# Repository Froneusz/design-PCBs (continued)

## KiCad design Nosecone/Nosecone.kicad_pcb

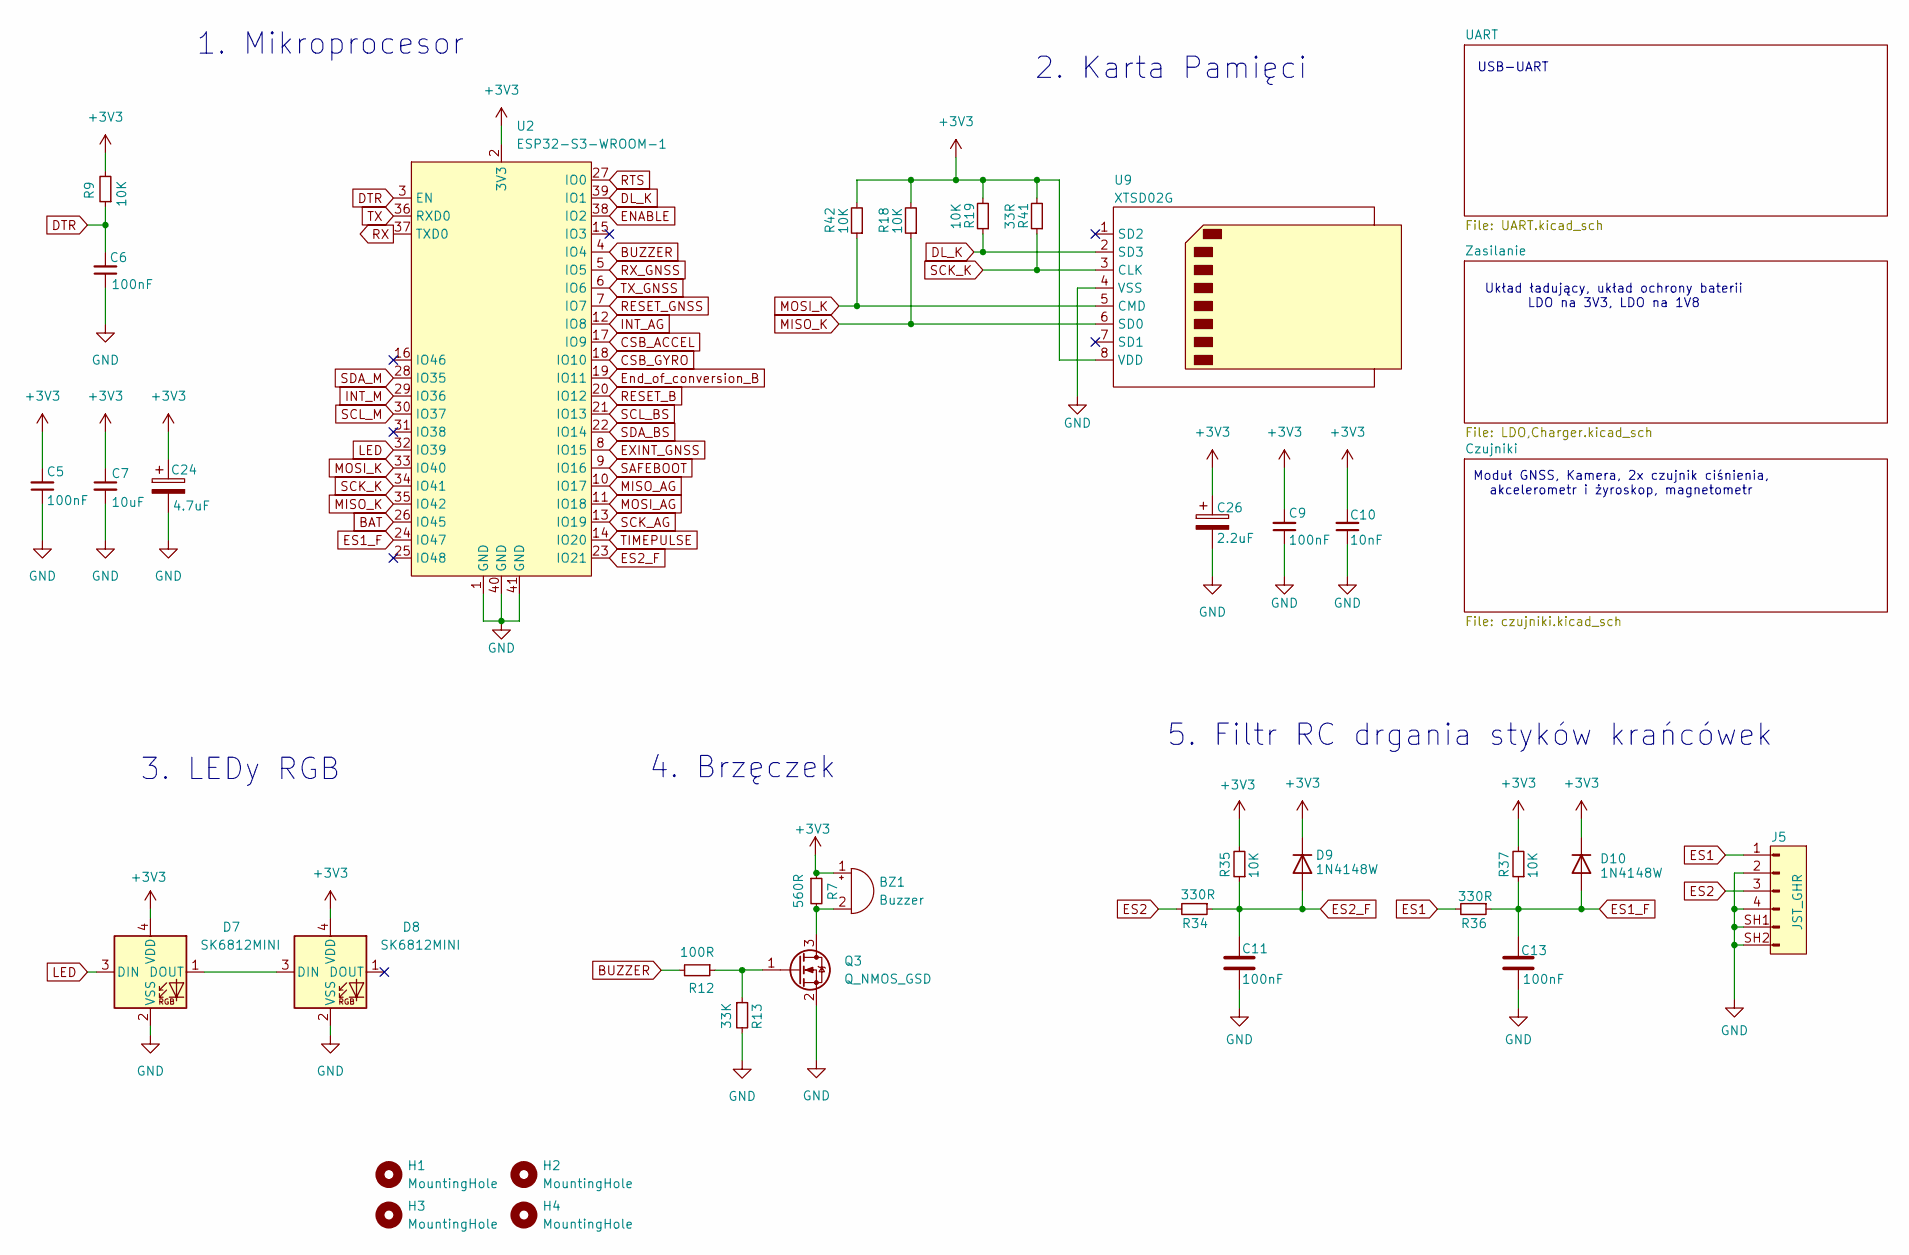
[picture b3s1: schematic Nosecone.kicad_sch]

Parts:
BZ1: Buzzer; CMT32265SMTTR
C5, C6, C9, C11, C13: 100nF; C_0402_1005Metric_Pad0.74x0.62mm_HandSolder
C7: 10uF; C_0402_1005Metric_Pad0.74x0.62mm_HandSolder
C10: 10nF; C_0402_1005Metric_Pad0.74x0.62mm_HandSolder
C24: 4.7uF; C_0402_1005Metric_Pad0.74x0.62mm_HandSolder
C26: 2.2uF; C_0402_1005Metric_Pad0.74x0.62mm_HandSolder
D7, D8: SK6812MINI; LED_SK6812MINI_PLCC4_3.5x3.5mm_P1.75mm
D9, D10: 1N4148W; D_SOD-123
H1, H2, H3, H4: MountingHole; MountingHole_3.2mm_M3_DIN965
J5: JST_GHR; JST_SM04B-GHS-TB(LF)(SN)-
Q3: Q_NMOS_GSD; SOT-23_Handsoldering
R7: 560R; R_0402_1005Metric_Pad0.72x0.64mm_HandSolder
R9, R18, R19, R35, R37, R42: 10K; R_0402_1005Metric_Pad0.72x0.64mm_HandSolder
R12: 100R; R_0402_1005Metric_Pad0.72x0.64mm_HandSolder
R13: 33K; R_0402_1005Metric_Pad0.72x0.64mm_HandSolder
R34, R36: 330R; R_0402_1005Metric_Pad0.72x0.64mm_HandSolder
R41: 33R; R_0402_1005Metric_Pad0.72x0.64mm_HandSolder
U2: ESP32-S3-WROOM-1
U9: XTSD02G; Bosch_LGA-8_2.5x2.5mm_P0.65mm_ClockwisePinNumbering

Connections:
+3V3: BZ1.1 (-), C5.2, C7.1, C9.2, C10.2, C24.1, C26.1, D7.4 (VDD), D8.4 (VDD), D9.1 (K), D10.1 (K), R7.1, R9.2, R18.2, R19.2, R35.2, R37.2, R41.2, R42.2, U2.2 (3V3), U9.8 (VDD); also elsewhere on the board
BAT: U2.26 (IO45); also elsewhere on the board
BUZZER: R12.2, U2.4 (IO4)
CSB_ACCEL: U2.17 (IO9); also elsewhere on the board
CSB_GYRO: U2.18 (IO10); also elsewhere on the board
DL_K: R19.1, U2.39 (IO1), U9.2 (SD3)
DTR: C6.2, R9.1, U2.3 (EN); also elsewhere on the board
ENABLE: U2.38 (IO2); also elsewhere on the board
ES1: J5.1, R36.2
ES1_F: C13.2, D10.2 (A), R36.1, R37.1, U2.24 (IO47)
ES2: J5.3, R34.2
ES2_F: C11.2, D9.2 (A), R34.1, R35.1, U2.23 (IO21)
EXINT_GNSS: U2.8 (IO15); also elsewhere on the board
End_of_conversion_B: U2.19 (IO11); also elsewhere on the board
GND: C5.1, C6.1, C7.2, C9.1, C10.1, C11.1, C13.1, C24.2, C26.2, D7.2 (VSS), D8.2 (VSS), J5.2, J5.4, J5.SH1 (Pin_5), J5.SH2 (Pin_6), Q3.2 (S), R13.2, U2.1 (GND), U2.40 (GND), U2.41 (GND), U9.4 (VSS); also elsewhere on the board
INT_AG: U2.12 (IO8); also elsewhere on the board
INT_M: U2.29 (IO36); also elsewhere on the board
LED: D7.3 (DIN), U2.32 (IO39)
MISO_AG: U2.10 (IO17); also elsewhere on the board
MISO_K: R18.1, U2.35 (IO42), U9.6 (SD0)
MOSI_AG: U2.11 (IO18); also elsewhere on the board
MOSI_K: R42.1, U2.33 (IO40), U9.5 (CMD)
unnamed: BZ1.2 (+), Q3.3 (D), R7.2
unnamed: D7.1 (DOUT), D8.3 (DIN)
unnamed: Q3.1 (G), R12.1, R13.1
RESET_B: U2.20 (IO12); also elsewhere on the board
RESET_GNSS: U2.7 (IO7); also elsewhere on the board
RTS: U2.27 (IO0); also elsewhere on the board
RX: U2.37 (TXD0); also elsewhere on the board
RX_GNSS: U2.5 (IO5); also elsewhere on the board
SAFEBOOT: U2.9 (IO16); also elsewhere on the board
SCK_AG: U2.13 (IO19); also elsewhere on the board
SCK_K: R41.1, U2.34 (IO41), U9.3 (CLK)
SCL_BS: U2.21 (IO13); also elsewhere on the board
SCL_M: U2.30 (IO37); also elsewhere on the board
SDA_BS: U2.22 (IO14); also elsewhere on the board
SDA_M: U2.28 (IO35); also elsewhere on the board
TIMEPULSE: U2.14 (IO20); also elsewhere on the board
TX: U2.36 (RXD0); also elsewhere on the board
TX_GNSS: U2.6 (IO6); also elsewhere on the board

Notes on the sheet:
1. Mikroprocesor
Moduł GNSS, Kamera, 2x czujnik ciśnienia, akcelerometr i żyroskop, magnetometr
Układ ładujący, układ ochrony baterii LDO na 3V3, LDO na 1V8
2. Karta Pamięci
USB-UART
3. LEDy RGB
4. Brzęczek
5. Filtr RC drgania styków krańcówek

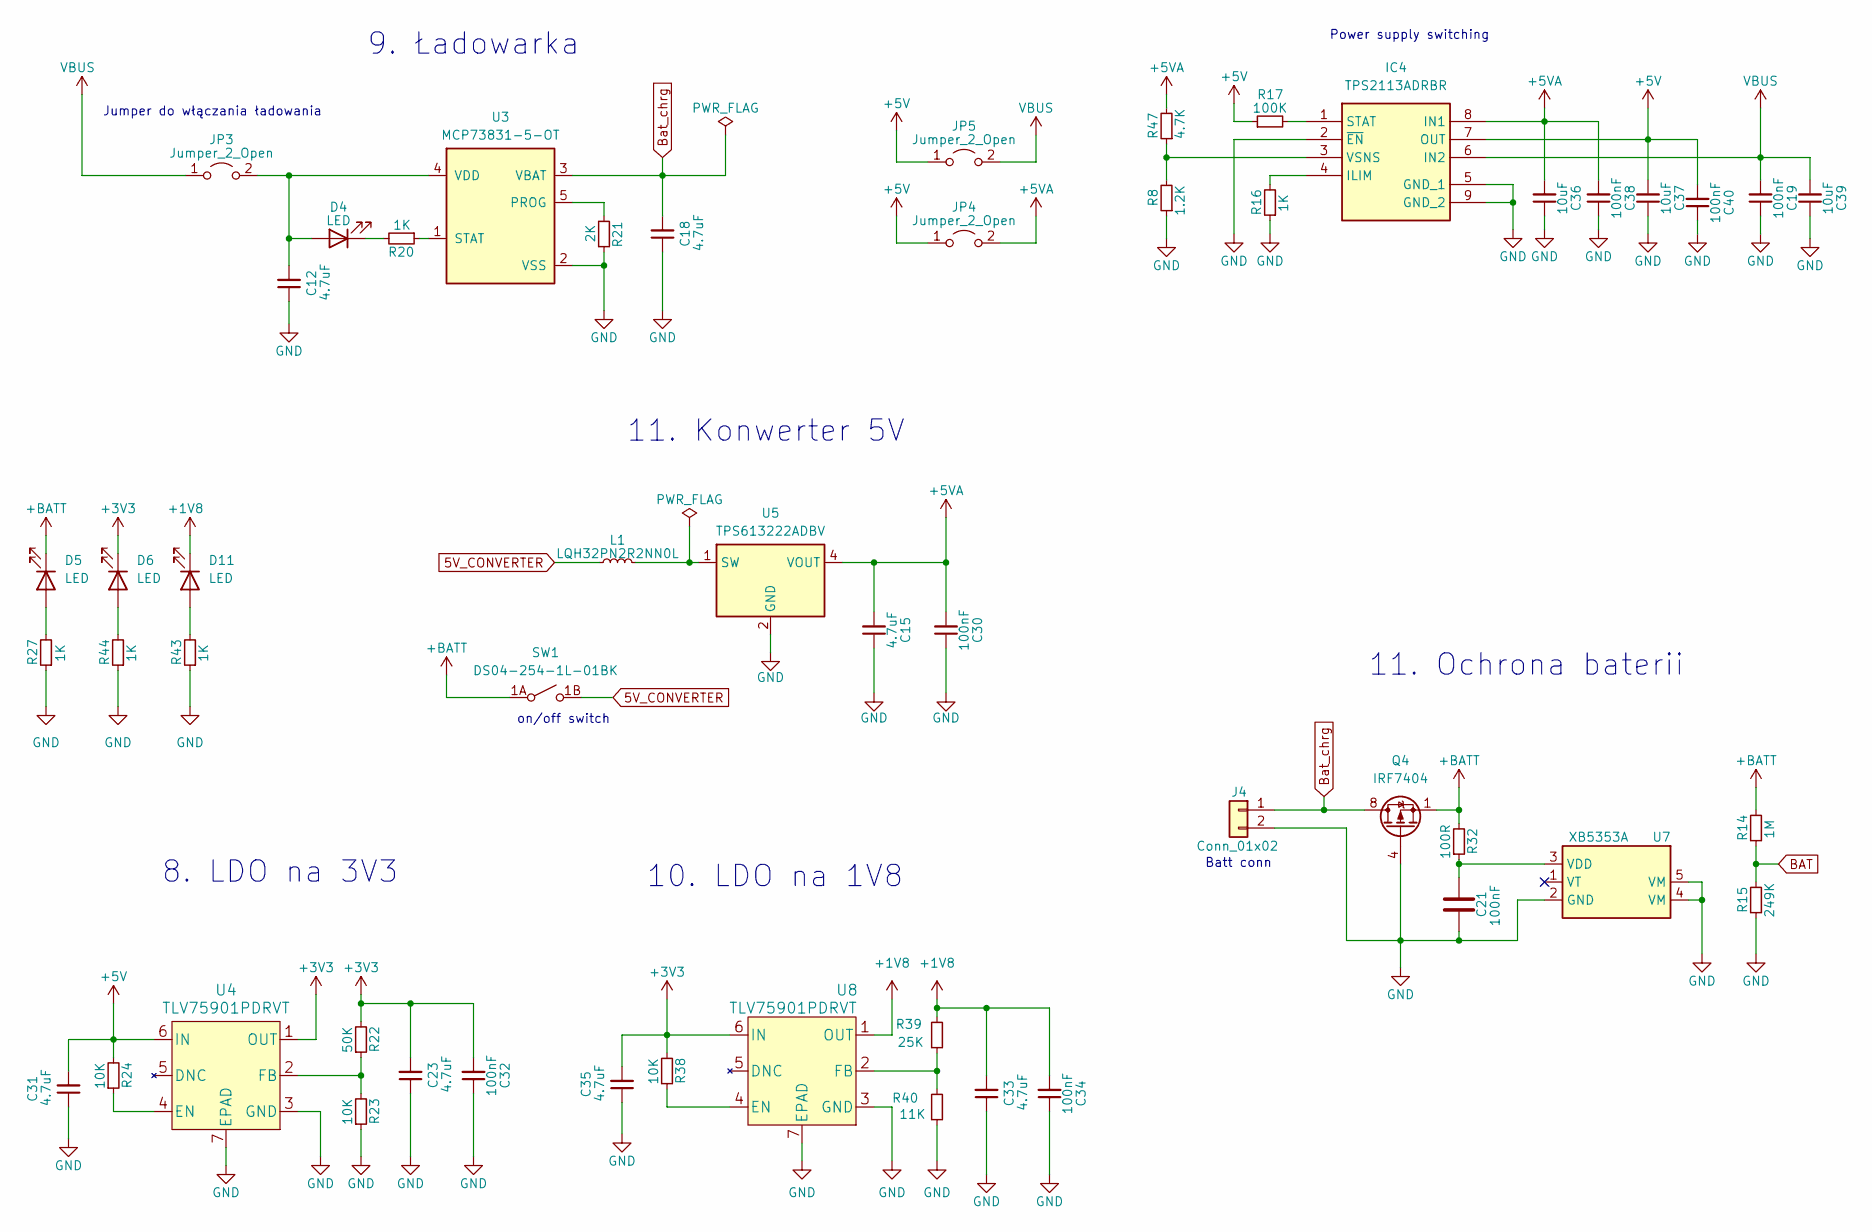
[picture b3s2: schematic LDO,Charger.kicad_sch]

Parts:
C12, C15, C18, C23, C31, C33, C35: 4.7uF; C_0402_1005Metric_Pad0.74x0.62mm_HandSolder
C19, C21, C30, C32, C34, C38, C40: 100nF; C_0402_1005Metric_Pad0.74x0.62mm_HandSolder
C36, C37, C39: 10uF; C_0402_1005Metric_Pad0.74x0.62mm_HandSolder
D4, D5, D6, D11: LED; LED_0603_1608Metric_Pad1.05x0.95mm_HandSolder
IC4: TPS2113ADRBR; SON65P300X300X100-9N-D; Mouser Part Number 595-TPS2113ADRBR
J4: Conn_01x02; Power_supply_2_PAD
JP3, JP4, JP5: Jumper_2_Open; SolderJumper-2_P1.3mm_Open_RoundedPad1.0x1.5mm
L1: LQH32PN2R2NN0L; LQH32CH100K53L
Q4: IRF7404; SOIC-8_3.9x4.9mm_P1.27mm
R8: 1.2K; R_0402_1005Metric_Pad0.72x0.64mm_HandSolder
R14: 1M; R_0402_1005Metric_Pad0.72x0.64mm_HandSolder
R15: 249K; R_0402_1005Metric_Pad0.72x0.64mm_HandSolder
R16, R20, R27, R43, R44: 1K; R_0402_1005Metric_Pad0.72x0.64mm_HandSolder
R17: 100K; R_0402_1005Metric_Pad0.72x0.64mm_HandSolder
R21: 2K; R_0402_1005Metric_Pad0.72x0.64mm_HandSolder
R22: 50K; R_0402_1005Metric_Pad0.72x0.64mm_HandSolder
R23, R24, R38: 10K; R_0402_1005Metric_Pad0.72x0.64mm_HandSolder
R32: 100R; R_0402_1005Metric_Pad0.72x0.64mm_HandSolder
R39: 25K; R_0402_1005Metric_Pad0.72x0.64mm_HandSolder
R40: 11K; R_0402_1005Metric_Pad0.72x0.64mm_HandSolder
R47: 4.7K; R_0402_1005Metric_Pad0.72x0.64mm_HandSolder
SW1: DS04-254-1L-01BK; SW_DS04-254-1L-01BK
U3: MCP73831-5-OT; SOT-23-5
U4, U8: TLV75901PDRVT
U5: TPS613222ADBV; SOT-23-5
U7: XB5353A; SOT-23-5

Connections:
5V_CONVERTER: L1.1, SW1.1B (B)
+1V8: C33.2, C34.2, D11.1 (K), R39.2, U8.1 (OUT); also elsewhere on the board
+3V3: C23.2, C32.2, C35.2, D6.1 (K), R22.2, R38.2, U4.1 (OUT), U8.6 (IN); also elsewhere on the board
+5V: C31.2, C37.2, C40.2, IC4.7 (OUT), JP4.1 (A), JP5.1 (A), R17.1, R24.2, U4.6 (IN); also elsewhere on the board
+5VA: C15.2, C30.2, C36.2, C38.2, IC4.8 (IN1), JP4.2 (B), R47.2, U5.4 (VOUT)
+BATT: D5.1 (K), Q4.1 (S), Q4.2 (S), Q4.3 (S), R14.2, R32.2, SW1.1A (A)
BAT: R14.1, R15.2; also elsewhere on the board
Bat_chrg: C18.2, J4.1, Q4.5 (D), Q4.6 (D), Q4.7 (D), Q4.8 (D), U3.3 (VBAT)
GND: C12.1, C15.1, C18.1, C19.1, C21.1, C23.1, C30.1, C31.1, C32.1, C33.1, C34.1, C35.1, C36.1, C37.1, C38.1, C39.1, C40.1, IC4.2 (~EN), IC4.5 (GND_1), IC4.9 (GND_2), J4.2, Q4.4 (G), R8.1, R15.1, R16.1, R21.2, R23.1, R27.1, R40.1, R43.1, R44.1, U3.2 (VSS), U4.3 (GND), U4.7 (EPAD), U5.2 (GND), U7.2 (GND), U7.4 (VM), U7.5 (VM), U8.3 (GND), U8.7 (EPAD); also elsewhere on the board
unnamed: C12.2, D4.2 (A), JP3.2 (B), U3.4 (VDD)
unnamed: D4.1 (K), R20.2
unnamed: D5.2 (A), R27.2
unnamed: D6.2 (A), R44.2
unnamed: D11.2 (A), R43.2
unnamed: IC4.4 (ILIM), R16.2
unnamed: IC4.1 (STAT), R17.2
unnamed: IC4.3 (VSNS), R8.2, R47.1
unnamed: R21.1, U3.5 (PROG)
unnamed: R20.1, U3.1 (STAT)
unnamed: R24.1, U4.4 (EN)
unnamed: R22.1, R23.2, U4.2 (FB)
unnamed: L1.2, U5.1 (SW)
unnamed: C21.2, R32.1, U7.3 (VDD)
unnamed: R38.1, U8.4 (EN)
unnamed: R39.1, R40.2, U8.2 (FB)
VBUS: C19.2, C39.2, IC4.6 (IN2), JP3.1 (A), JP5.2 (B); also elsewhere on the board

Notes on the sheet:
11. Ochrona baterii
Batt conn
Power supply switching
Jumper do włączania ładowania
11. Konwerter 5V
9. Ładowarka
on/off switch
8. LDO na 3V3
10. LDO na 1V8

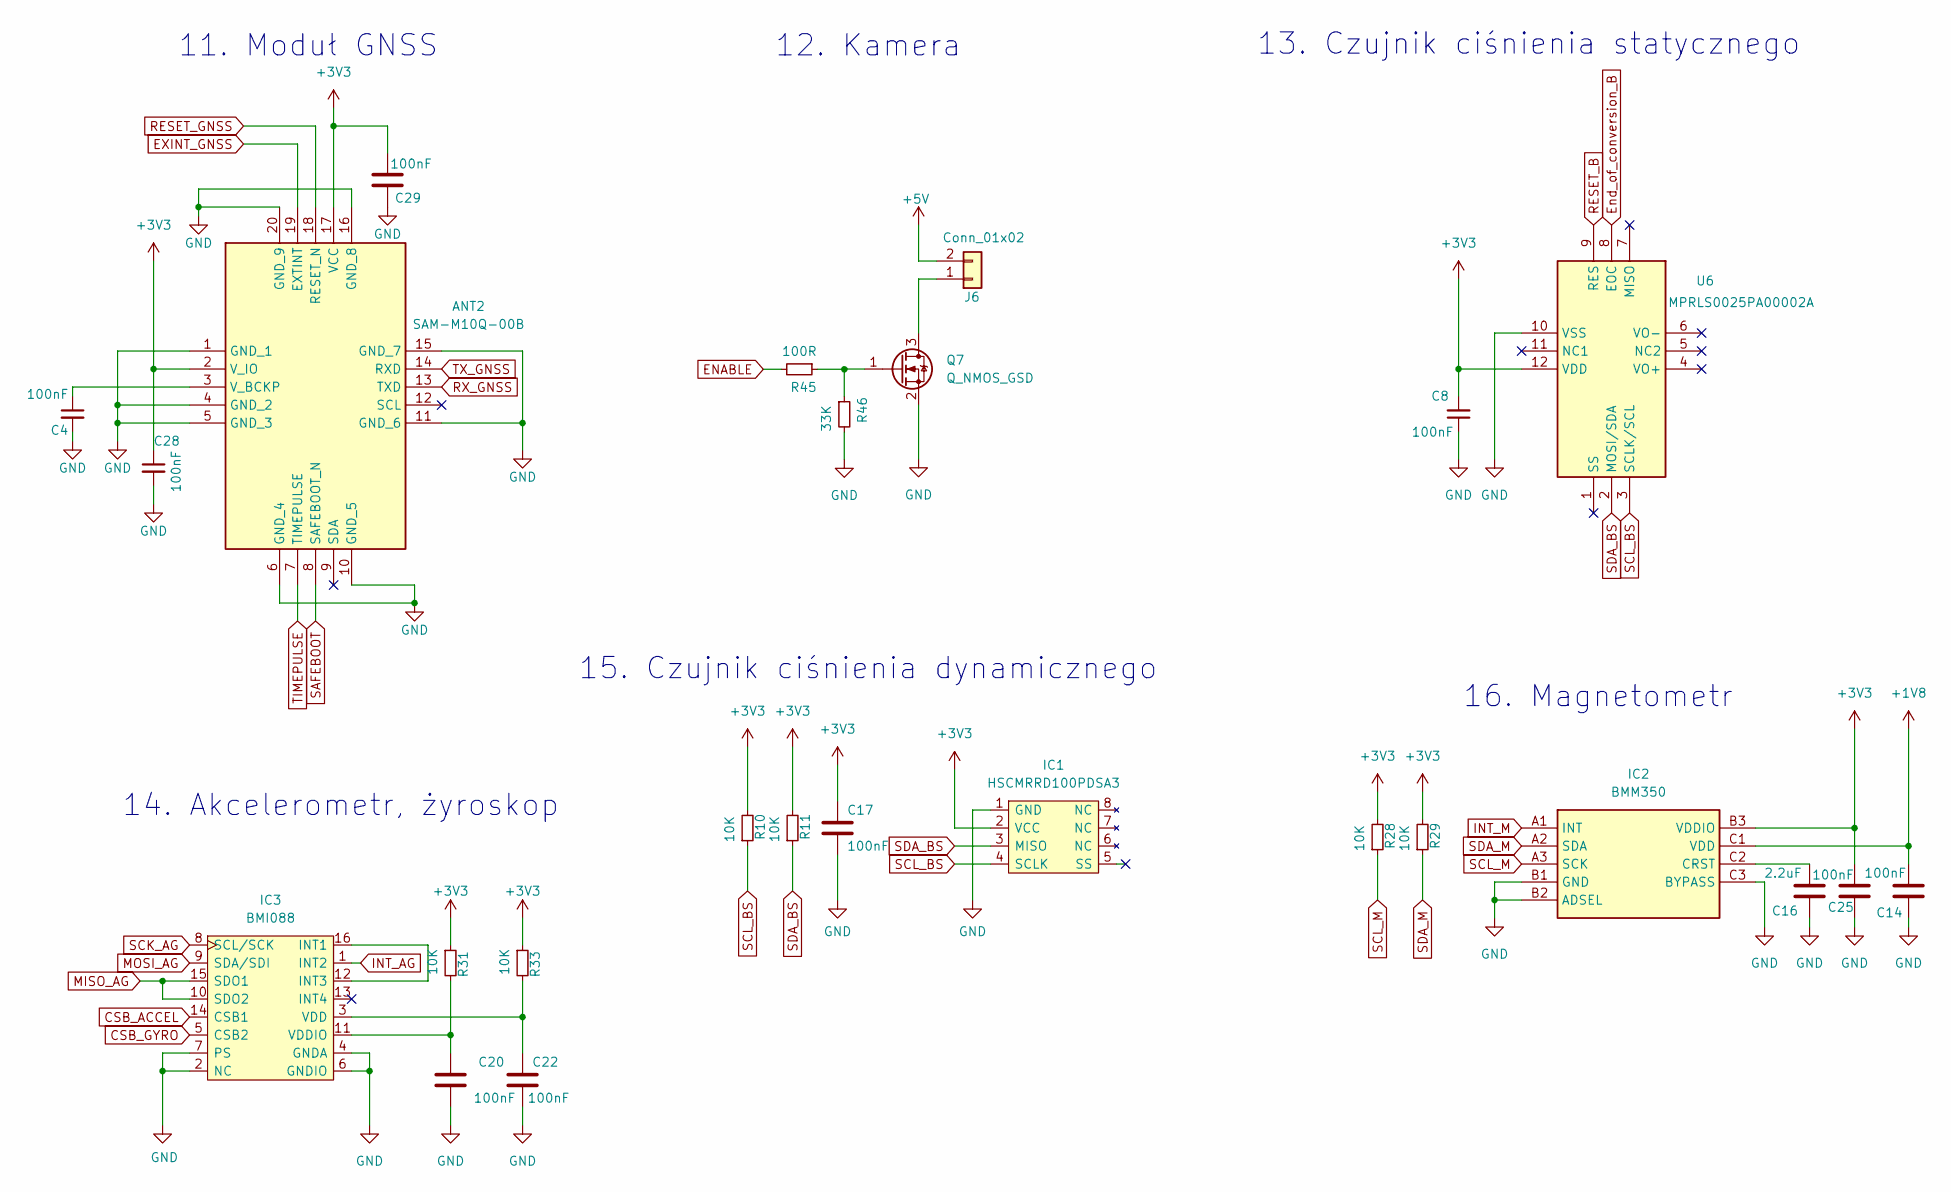
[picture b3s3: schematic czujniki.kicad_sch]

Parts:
ANT2: SAM-M10Q-00B; SAMM10Q00B; Mouser Part Number 377-SAM-M10Q-00B
C4, C8, C14, C17, C20, C22, C25, C28, C29: 100nF; C_0402_1005Metric_Pad0.74x0.62mm_HandSolder
C16: 2.2uF; C_0402_1005Metric_Pad0.74x0.62mm_HandSolder
IC1: HSCMRRD100PDSA3; Manufacturer_Part_Number HSCMRRD100PDSA3
IC2: BMM350; BGA9C40P3X3_128X128X54; Mouser Part Number 262-BMM350
IC3: BMI088; PQFN50P450X300X100-16N
J6: Conn_01x02; Power_supply_2_PAD
Q7: Q_NMOS_GSD; SOT-23_Handsoldering
R10, R11, R28, R29, R31, R33: 10K; R_0402_1005Metric_Pad0.72x0.64mm_HandSolder
R45: 100R; R_0402_1005Metric_Pad0.72x0.64mm_HandSolder
R46: 33K; R_0402_1005Metric_Pad0.72x0.64mm_HandSolder
U6: MPRLS0025PA00002A; MPRLS0025PA00001A; Mouser Part Number 785-MPRLS0025PA00001

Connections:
+1V8: C14.1, IC2.C1 (VDD); also elsewhere on the board
+3V3: ANT2.2 (V_IO), ANT2.17 (VCC), C8.2, C17.2, C25.1, C28.1, C29.1, IC1.2 (VCC), IC2.B3 (VDDIO), R10.2, R11.2, R28.2, R29.2, R31.1, R33.1, U6.12 (VDD); also elsewhere on the board
+5V: J6.2; also elsewhere on the board
CSB_ACCEL: IC3.14 (CSB1); also elsewhere on the board
CSB_GYRO: IC3.5 (CSB2); also elsewhere on the board
ENABLE: R45.2; also elsewhere on the board
EXINT_GNSS: ANT2.19 (EXTINT); also elsewhere on the board
End_of_conversion_B: U6.8 (EOC); also elsewhere on the board
GND: ANT2.1 (GND_1), ANT2.4 (GND_2), ANT2.5 (GND_3), ANT2.6 (GND_4), ANT2.10 (GND_5), ANT2.11 (GND_6), ANT2.15 (GND_7), ANT2.16 (GND_8), ANT2.20 (GND_9), C4.2, C8.1, C14.2, C16.2, C17.1, C20.1, C22.1, C25.2, C28.2, C29.2, IC1.1 (GND), IC2.B1 (GND), IC2.B2 (ADSEL), IC2.C3 (BYPASS), IC3.2 (NC), IC3.4 (GNDA), IC3.6 (GNDIO), IC3.7 (PS), Q7.2 (S), R46.2, U6.10 (VSS); also elsewhere on the board
INT_AG: IC3.1 (INT2); also elsewhere on the board
INT_M: IC2.A1 (INT); also elsewhere on the board
MISO_AG: IC3.10 (SDO2), IC3.15 (SDO1); also elsewhere on the board
MOSI_AG: IC3.9 (SDA/SDI); also elsewhere on the board
unnamed: ANT2.3 (V_BCKP), C4.1
unnamed: C16.1, IC2.C2 (CRST)
unnamed: IC3.12 (INT3), IC3.16 (INT1)
unnamed: C22.2, IC3.3 (VDD), R33.2
unnamed: C20.2, IC3.11 (VDDIO), R31.2
unnamed: J6.1, Q7.3 (D)
unnamed: Q7.1 (G), R45.1, R46.1
RESET_B: U6.9 (RES); also elsewhere on the board
RESET_GNSS: ANT2.18 (RESET_N); also elsewhere on the board
RX_GNSS: ANT2.13 (TXD); also elsewhere on the board
SAFEBOOT: ANT2.8 (SAFEBOOT_N); also elsewhere on the board
SCK_AG: IC3.8 (SCL/SCK); also elsewhere on the board
SCL_BS: IC1.4 (SCLK), R10.1, U6.3 (SCLK/SCL); also elsewhere on the board
SCL_M: IC2.A3 (SCK), R28.1; also elsewhere on the board
SDA_BS: IC1.3 (MISO), R11.1, U6.2 (MOSI/SDA); also elsewhere on the board
SDA_M: IC2.A2 (SDA), R29.1; also elsewhere on the board
TIMEPULSE: ANT2.7 (TIMEPULSE); also elsewhere on the board
TX_GNSS: ANT2.14 (RXD); also elsewhere on the board

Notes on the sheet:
12. Kamera
13. Czujnik ciśnienia statycznego
15. Czujnik ciśnienia dynamicznego
14. Akcelerometr, żyroskop
16. Magnetometr
11. Moduł GNSS

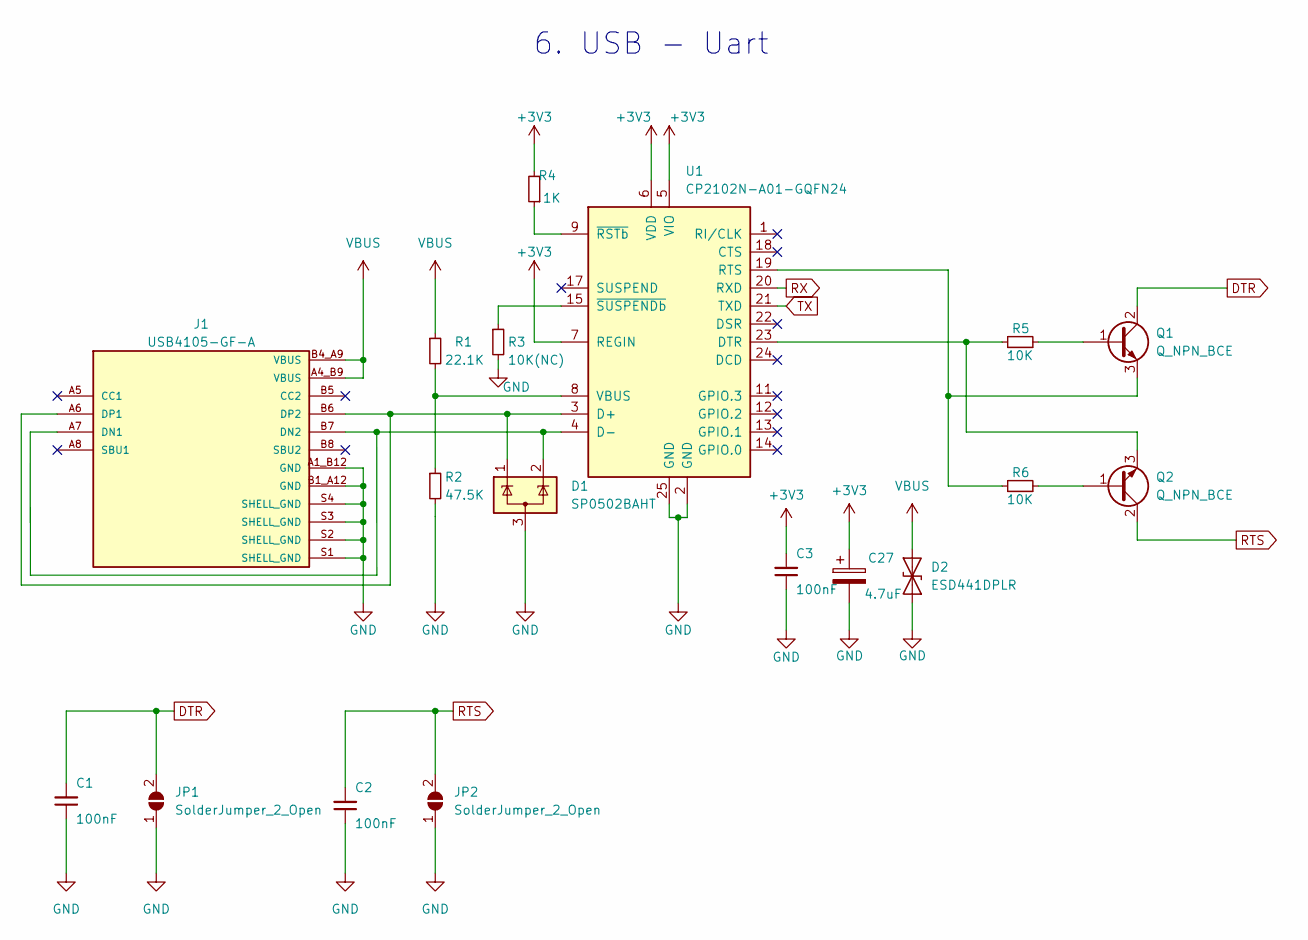
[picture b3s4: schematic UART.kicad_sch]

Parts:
C1, C2, C3: 100nF; C_0402_1005Metric_Pad0.74x0.62mm_HandSolder
C27: 4.7uF; C_0402_1005Metric_Pad0.74x0.62mm_HandSolder
D1: SP0502BAHT; SOT-23
D2: ESD441DPLR; D_0201_0603Metric_Pad0.64x0.40mm_HandSolder
J1: USB4105-GF-A; GCT_USB4105-GF-A; PARTREV A3
JP1, JP2: SolderJumper_2_Open; SolderJumper-2_P1.3mm_Open_RoundedPad1.0x1.5mm
Q1, Q2: Q_NPN_BCE; SOT-23_Handsoldering
R1: 22.1K; R_0402_1005Metric_Pad0.72x0.64mm_HandSolder
R2: 47.5K; R_0402_1005Metric_Pad0.72x0.64mm_HandSolder
R3: 10K(NC); R_0402_1005Metric_Pad0.72x0.64mm_HandSolder
R4: 1K; R_0402_1005Metric_Pad0.72x0.64mm_HandSolder
R5, R6: 10K; R_0402_1005Metric_Pad0.72x0.64mm_HandSolder
U1: CP2102N-A01-GQFN24; QFN-24-1EP_4x4mm_P0.5mm_EP2.6x2.6mm

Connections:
+3V3: C3.2, C27.1, R4.2, U1.5 (VIO), U1.6 (VDD), U1.7 (REGIN); also elsewhere on the board
DTR: C1.2, JP1.2 (B), Q1.2 (C); also elsewhere on the board
GND: C1.1, C2.1, C3.1, C27.2, D1.3 (A), D2.1 (A1), J1.A1_B12 (GND), J1.B1_A12 (GND), J1.S1 (SHELL_GND), J1.S2 (SHELL_GND), J1.S3 (SHELL_GND), J1.S4 (SHELL_GND), JP1.1 (A), JP2.1 (A), R2.2, R3.2, U1.2 (GND), U1.25 (GND); also elsewhere on the board
unnamed: D1.2 (K), J1.A7 (DN1), J1.B7 (DN2), U1.4 (D-)
unnamed: D1.1 (K), J1.A6 (DP1), J1.B6 (DP2), U1.3 (D+)
unnamed: Q1.1 (B), R5.2
unnamed: Q1.3 (E), R6.1, U1.19 (RTS)
unnamed: Q2.1 (B), R6.2
unnamed: Q2.3 (E), R5.1, U1.23 (DTR)
unnamed: R1.2, R2.1, U1.8 (VBUS)
unnamed: R4.1, U1.9 (~RSTb)
unnamed: R3.1, U1.15 (~SUSPENDb)
RTS: C2.2, JP2.2 (B), Q2.2 (C); also elsewhere on the board
RX: U1.20 (RXD); also elsewhere on the board
TX: U1.21 (TXD); also elsewhere on the board
VBUS: D2.2 (A2), J1.A4_B9 (VBUS), J1.B4_A9 (VBUS), R1.1; also elsewhere on the board

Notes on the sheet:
6. USB - Uart

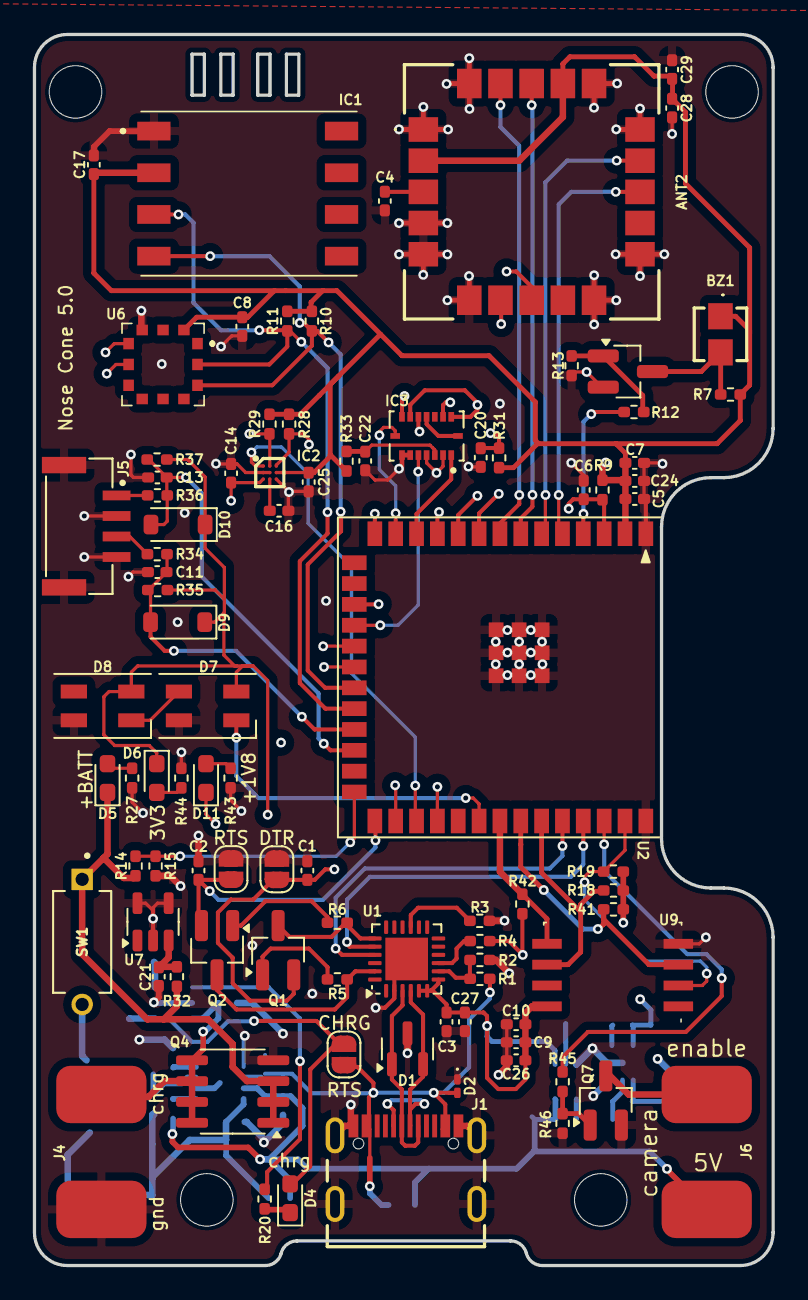
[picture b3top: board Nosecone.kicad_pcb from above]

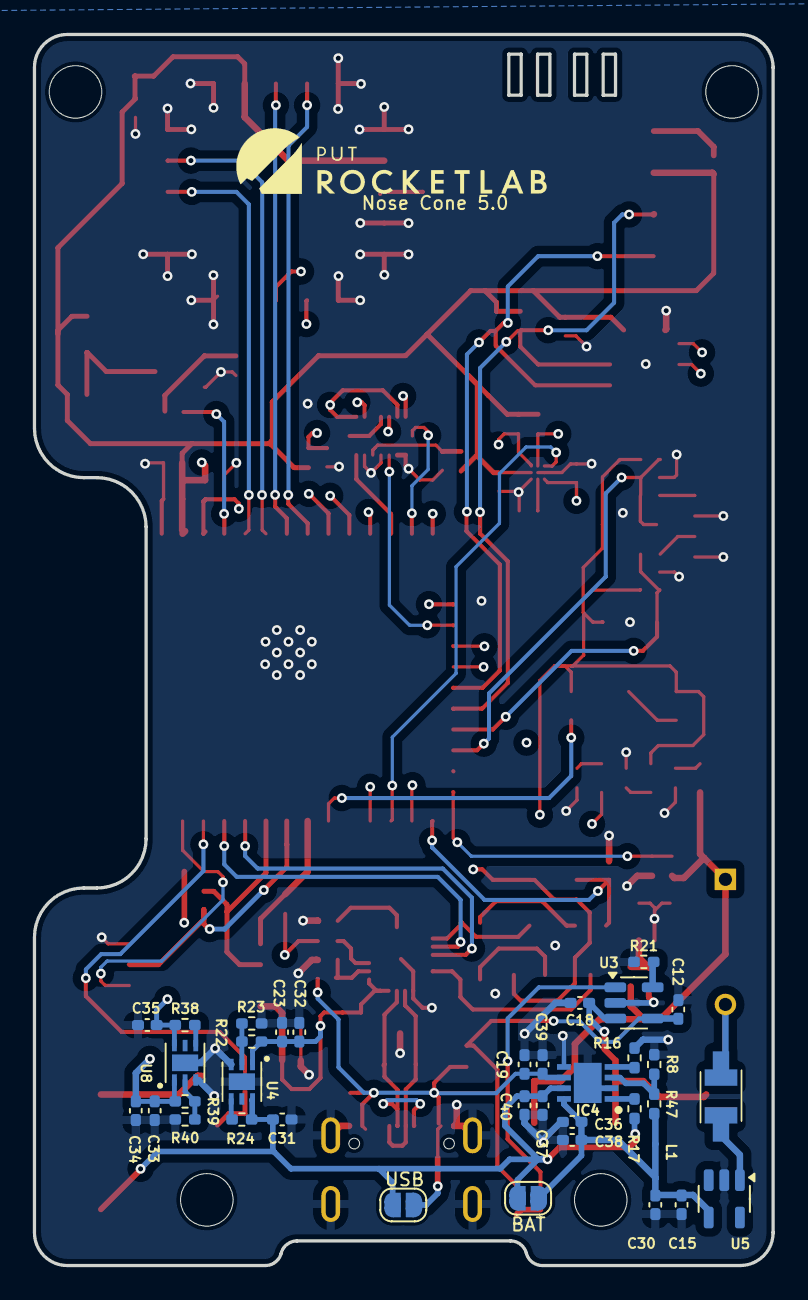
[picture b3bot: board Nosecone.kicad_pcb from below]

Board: 4 copper layers, 45.0 x 75.0 mm, 129 parts (35 on the bottom side), 79 nets.

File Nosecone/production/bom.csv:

Designator,Footprint,Quantity,Value,LCSC Part #
ANT2,SAMM10Q00B,1,SAM-M10Q-00B,
BZ1,CMT32265SMTTR,1,Buzzer,
"C1, C11, C13, C14, C17, C19, C2, C20, C21, C22, C25, C28, C29, C3, C30, C32, C34, C38, C4, C40, C5, C6, C8, C9",0402,24,100nF,
C10,0402,1,10nF,
"C12, C15, C18, C23, C24, C27, C31, C33, C35",0402,9,4.7uF,
"C16, C26",0402,2,2.2uF,
"C36, C37, C39, C7",0402,4,10uF,
D1,SOT-23,1,SP0502BAHT,
"D10, D9",D_SOD-123,2,1N4148W,
"D11, D4, D5, D6",0603,4,LED,
D2,0201,1,ESD441DPLR,
"D7, D8",LED_SK6812MINI_PLCC4_3.5x3.5mm_P1.75mm,2,SK6812MINI,
"H1, H2, H3, H4",MountingHole_3.2mm_M3_DIN965,4,MountingHole,
IC1,HSCMRRD100PDSA3,1,HSCMRRD100PDSA3,
IC2,BGA9C40P3X3_128X128X54,1,BMM350,
IC3,PQFN50P450X300X100-16N,1,BMI088,
IC4,SON65P300X300X100-9N-D,1,TPS2113ADRBR,
J1,GCT_USB4105-GF-A,1,USB4105-GF-A,
"J4, J6",Power_supply_2_PAD,2,Conn_01x02,
J5,JST_SM04B-GHS-TB(LF)(SN)-,1,JST_GHR,
"JP1, JP2",SolderJumper-2_P1.3mm_Open_RoundedPad1.0x1.5mm,2,SolderJumper_2_Open,
"JP3, JP4, JP5",SolderJumper-2_P1.3mm_Open_RoundedPad1.0x1.5mm,3,Jumper_2_Open,
L1,LQH32CH100K53L,1,LQH32PN2R2NN0L,
"Q1, Q2",SOT-23_Handsoldering,2,Q_NPN_BCE,
"Q3, Q7",SOT-23_Handsoldering,2,Q_NMOS_GSD,
Q4,SOIC-8_3.9x4.9mm_P1.27mm,1,IRF7404,
R1,0402,1,22.1K,
"R10, R11, R18, R19, R23, R24, R28, R29, R31, R33, R35, R37, R38, R42, R5, R6, R9",0402,17,10K,
"R12, R32, R45",0402,3,100R,
"R13, R46",0402,2,33K,
R14,0402,1,1M,
R15,0402,1,249K,
"R16, R20, R27, R4, R43, R44",0402,6,1K,
R17,0402,1,100K,
R2,0402,1,47.5K,
R21,0402,1,2K,
R22,0402,1,50K,
R3,0402,1,10K(NC),
"R34, R36",0402,2,330R,
R39,0402,1,25K,
R40,0402,1,11K,
R41,0402,1,33R,
R47,0402,1,4.7K,
R7,0402,1,560R,
R8,0402,1,1.2K,
SW1,SW_DS04-254-1L-01BK,1,DS04-254-1L-01BK,
U1,QFN-24-1EP_4x4mm_P0.5mm_EP2.6x2.6mm,1,CP2102N-A01-GQFN24,
U2,ESP32-S3-WROOM-1,1,ESP32-S3-WROOM-1,
U3,SOT-23-5,1,MCP73831-5-OT,
"U4, U8",TLV75901PDRVT,2,TLV75901PDRVT,
U5,SOT-23-5,1,TPS613222ADBV,
U6,MPRLS0025PA00001A,1,MPRLS0025PA00002A,
U7,SOT-23-5,1,XB5353A,
U9,Bosch_LGA-8_2.5x2.5mm_P0.65mm_ClockwisePinNumbering,1,XTSD02G,

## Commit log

2025-07-31 all files
2025-07-31 nosecone project
2025-07-31 add cordless_igniter,ballmill,rotor_board
